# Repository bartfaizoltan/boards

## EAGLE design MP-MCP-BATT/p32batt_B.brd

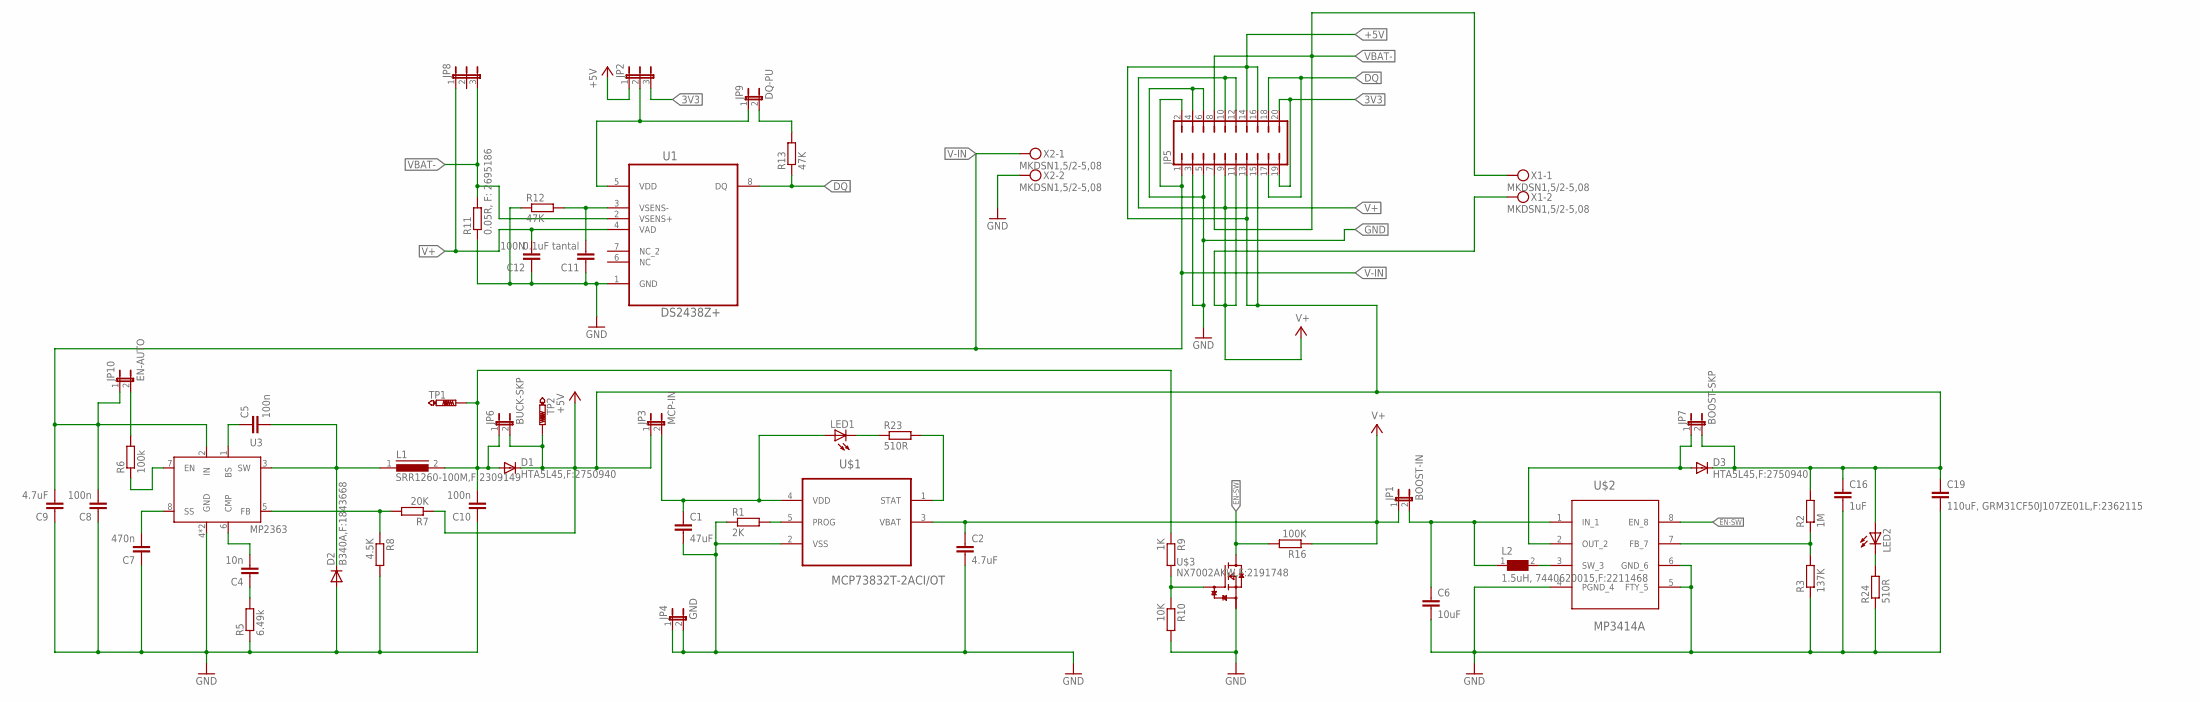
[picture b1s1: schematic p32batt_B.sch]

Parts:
C1: 47uF; C1206
C2, C9: 4.7uF; C1206
C4: 10n; C0805
C5, C8, C10: 100n; C0805
C6: 10uF; C1206
C7: 470n; C0805
C11: 0.1uF tantal; C0805
C12: 100N; C0805
C16: 1uF; C1206
C19: 110uF, GRM31CF50J107ZE01L,F:2362115; C1206
D1, D3: HTA5L45,F:2750940; DO214AC
D2: B340A,F:1843668; DO214AC
JP1: BOOST-IN; JP1
JP2, JP8: JP2E; JP2
JP3: MCP-IN; JP1
JP4: GND; JP1
JP5: JP10Q
JP6: BUCK-SKP; JP1
JP7: BOOST-SKP; JP1
JP9: DQ-PU; JP1
JP10: EN-AUTO; JP1
L1: SRR1260-100M,F:2309149; SRR1210
L2: 1.5uH, 7440620015,F:2211468; WE-TPC_6823
LED1, LED2: LEDCHIPLED_0805; CHIPLED_0805
R1: 2K; R0805
R2: 1M; R0805
R3: 137K; R0805
R5: 6.49k; R0805
R6: 100k; R0805
R7: 20K; R0805
R8: 4.5K; R0805
R9: 1K; R0805
R10: 10K; R0805
R11: 0.05R, F: 2695186; R2512
R12, R13: 47K; R0805
R16: 100K; R0805
R23, R24: 510R; R0805
TP1, TP2: PTR1PAD1-13; P1-13
U1: DS2438Z+; SOIC127P600X175-8N
U3: MP2363; SOIC8E
U$1: MCP73832T-2ACI/OT; SOT95P280X145-5N
U$2: MP3414A; TSOT23-8
U$3: NX7002AKW,F:2191748; SOT323
X1, X2: MKDSN1,5/2-5,08

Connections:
3V3: JP2.3, JP5.19, JP5.20
+5V: C16.1, C19.1, D1.C, D3.C, JP2.1, JP3.1, JP5.13, JP5.14, JP5.15, JP5.16, JP6.2, JP7.2, LED2.A, R2.2, R7.1, TP2.TP
DQ: JP5.17, JP5.18, R13.1, U1.8 (DQ)
EN-SW: R16.2, U$2.8 (EN_8), U$3.3 (D)
GND: C1.2, C2.2, C6.2, C7.1, C8.1, C9.1, C10.1, C11.1, C12.1, C16.2, C19.2, D2.A, JP4.1, JP4.2, JP5.3, JP5.4, JP5.5, JP5.6, R1.1, R3.1, R5.1, R8.2, R10.2, R11.1, R12.1, R24.1, U1.1 (GND), U3.4 (GND), U3.9 (GND), U$1.2 (VSS), U$2.4 (PGND_4), U$2.5 (FTY_5), U$2.6 (GND_6), U$3.2 (S), X2.2
unnamed: R1.2, U$1.5 (PROG)
unnamed: R2.1, R3.2, U$2.7 (FB_7)
unnamed: L2.2, U$2.3 (SW_3)
unnamed: D3.A, JP7.1, U$2.2 (OUT_2)
unnamed: LED2.C, R24.2
unnamed: R9.2, R10.1, U$3.1 (G)
unnamed: R23.2, U$1.1 (STAT)
unnamed: C1.1, JP3.2, LED1.A, U$1.4 (VDD)
unnamed: LED1.C, R23.1
unnamed: JP9.2, R13.2
unnamed: R6.1, U3.7 (EN)
unnamed: C4.2, U3.6 (CMP)
unnamed: C4.1, R5.2
unnamed: R7.2, R8.1, U3.5 (FB)
unnamed: C6.1, JP1.2, L2.1, U$2.1 (IN_1)
unnamed: JP2.2, JP9.1, U1.5 (VDD)
unnamed: JP10.2, R6.2
unnamed: C5.1, U3.1 (BS)
unnamed: C5.2, D2.C, L1.1, U3.3 (SW)
unnamed: C7.2, U3.8 (SS)
unnamed: C10.2, D1.A, JP6.1, L1.2, R9.1, TP1.TP
unnamed: C11.2, R12.2, U1.3 (VSENS-)
V+: C2.1, C12.2, JP1.1, JP5.9, JP5.10, JP5.11, JP5.12, JP8.1, R16.1, U1.4 (VAD), U$1.3 (VBAT), X1.2
V-IN: C8.2, C9.2, JP5.1, JP5.2, JP10.1, U3.2 (IN), X2.1
VBAT-: JP5.7, JP5.8, JP8.3, R11.2, U1.2 (VSENS+), X1.1

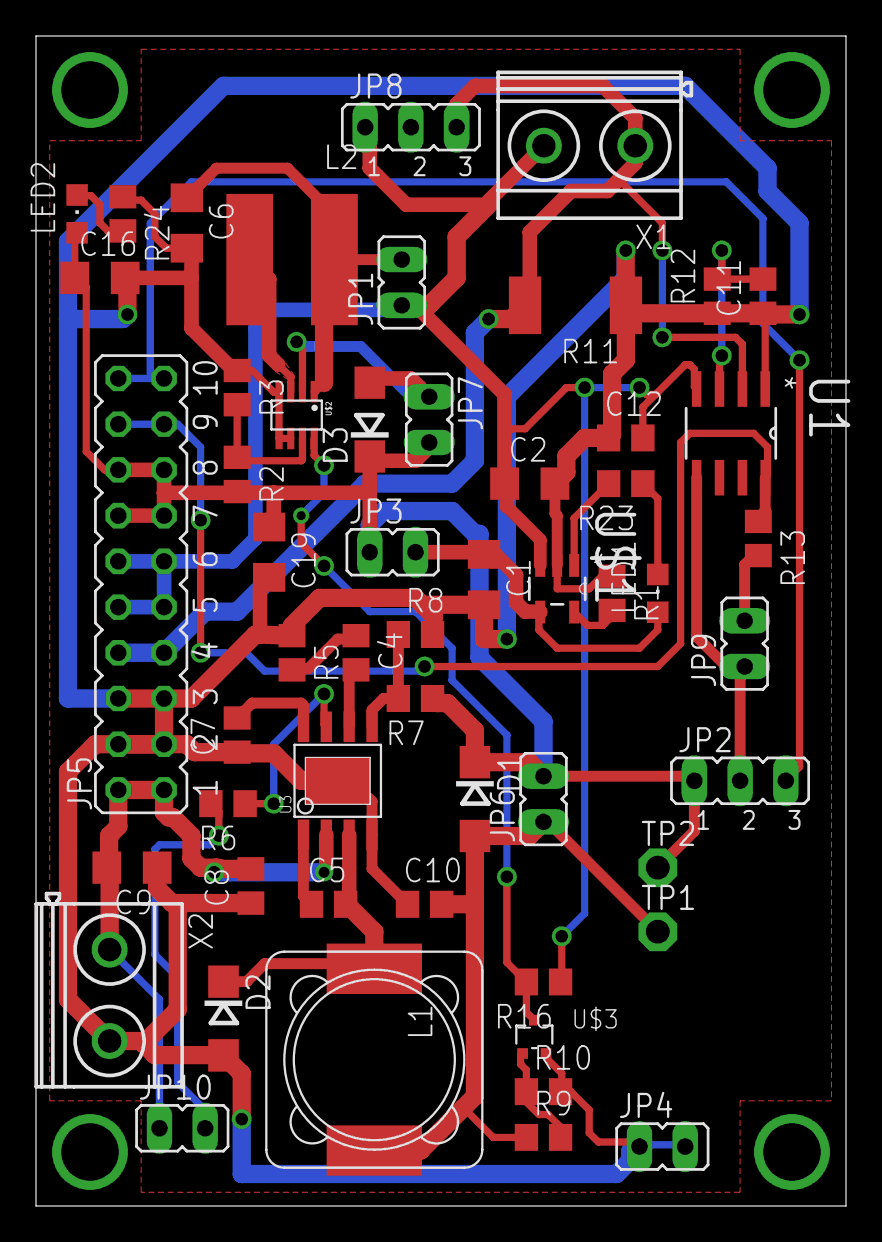
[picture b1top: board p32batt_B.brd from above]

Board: 2 copper layers, 44.9 x 64.9 mm, 54 parts (0 on the bottom side), 30 nets.

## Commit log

2017-12-08 first ver
2017-12-08 Pocket adding
2017-12-08 pocket again
